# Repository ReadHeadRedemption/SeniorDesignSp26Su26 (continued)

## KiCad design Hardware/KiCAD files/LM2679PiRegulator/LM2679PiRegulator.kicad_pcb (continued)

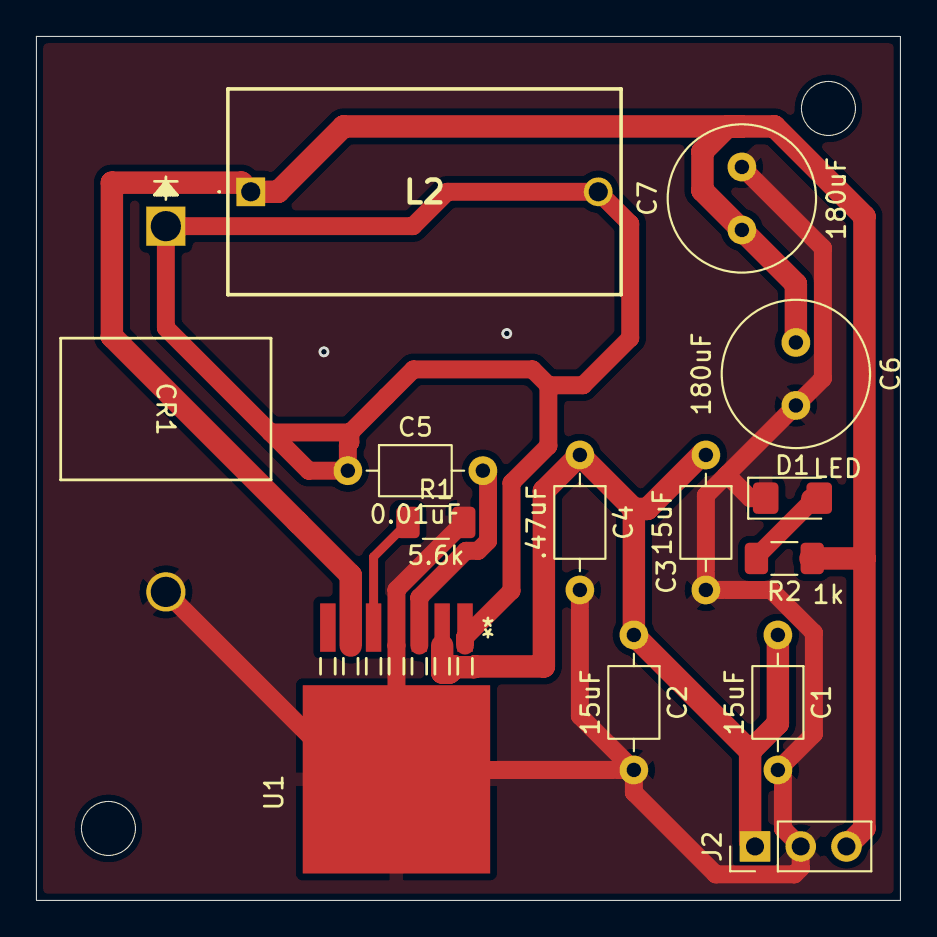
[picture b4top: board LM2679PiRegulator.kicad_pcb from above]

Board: 2 copper layers, 48.0 x 48.0 mm, 14 parts (0 on the bottom side), 7 nets.

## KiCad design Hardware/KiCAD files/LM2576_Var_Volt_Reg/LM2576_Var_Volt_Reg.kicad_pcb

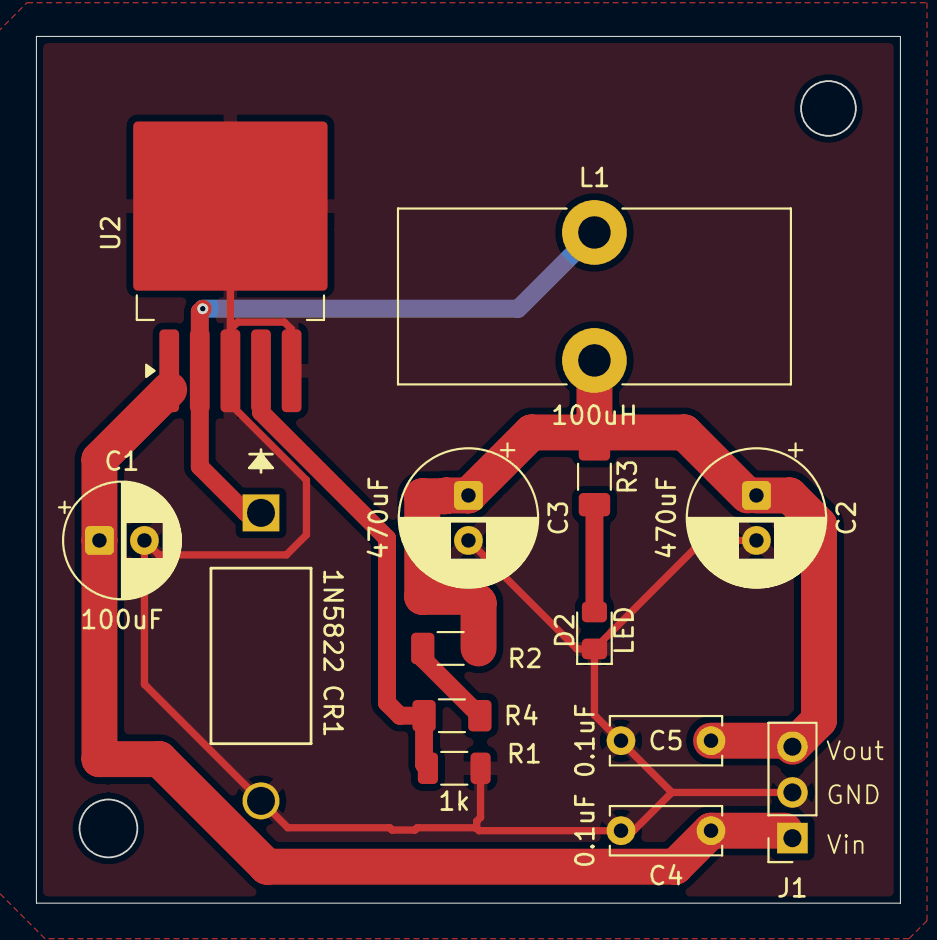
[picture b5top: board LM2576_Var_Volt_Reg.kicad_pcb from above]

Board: 2 copper layers, 48.0 x 48.2 mm, 14 parts (0 on the bottom side), 7 nets.

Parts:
C1: 100uF; CP_Radial_D6.3mm_P2.50mm
C2, C3: 470uF; CP_Radial_D7.5mm_P2.50mm
C4, C5: 0.1uF; C_Disc_D6.0mm_W2.5mm_P5.00mm
CR1: 1N5822; DO-201AD_STM
D2: LED; LED_0805_2012Metric_Pad1.15x1.40mm_HandSolder
J1: Conn_01x03_Pin; PinSocket_1x03_P2.54mm_Vertical
L1: 100uH; L_Toroid_Vertical_L21.6mm_W9.5mm_P7.11mm_Pulse_C
R1: 1k; R_1206_3216Metric
R2: Rvar; R_1206_3216Metric_Pad1.30x1.75mm_HandSolder
R3: 1k; R_1206_3216Metric_Pad1.30x1.75mm_HandSolder
R4: Ropt; R_1206_3216Metric_Pad1.30x1.75mm_HandSolder
U2: LM2576HVS-ADJ; TO-263-5_TabPin3

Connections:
/FB: R1.1, R4.2, U2.4 (FB)
/Vin: C1.1, C4.1, J1.1, U2.1 (VIN)
/Vout: C2.1, C3.1, C5.1, J1.3, L1.2, R2.1, R3.1
GND: C1.2, C2.2, C3.2, C4.2, C5.2, CR1.2, D2.1 (K), J1.2, R1.2, U2.3 (GND), U2.5 (~ON/OFF)
unnamed: D2.2 (A), R3.2
unnamed: R2.2, R4.1
unnamed: CR1.1, L1.1, U2.2 (OUT)

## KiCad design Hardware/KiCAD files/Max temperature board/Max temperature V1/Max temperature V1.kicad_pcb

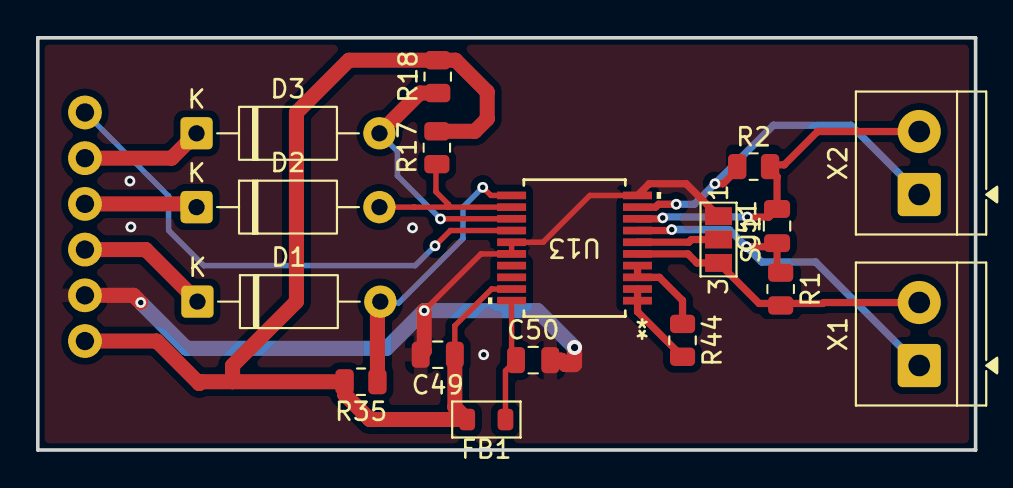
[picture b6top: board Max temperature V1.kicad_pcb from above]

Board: 2 copper layers, 52.1 x 22.9 mm, 18 parts (0 on the bottom side), 17 nets.

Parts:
C49, C50: 0.1uF; C_0805_2012Metric
C51: 100nF; C_0805_2012Metric
D1, D2, D3: 1N4148 eq.; D_A-405_P10.16mm_Horizontal
FB1: FERRITE-0805NO; Ferrite_0805_2012Metric
J1: Conn_01x06; 1x06_P2.54mm
R1, R2: 0ohm; R_0805_2012Metric
R17, R18, R35: 10K; R_0805_2012Metric
R44: 430Ω / 4300Ω 0.1%; R_0805_2012Metric
SJ1: SOLDERJUMPER_2WAY; SolderJumper-3_P1.3mm_Open_Pad1.0x1.5mm_NumberLabels
U13: MAX31865; 21-0056C_20_MXM
X1, X2: 3.5mm; TerminalBlock_4Ucon_1x02_P3.50mm_Horizontal

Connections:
+3.3V: C49.1, FB1.2, J1.6, R17.2, R18.2, R35.2, U13.19 (DVDD)
/CHAINL0_MISO_1: D1.1 (K), J1.4
/MISO_1: J1.1, U13.14 (SDO)
/SPI1_CLK: D2.1 (K), J1.3
/SPI1_CS: D3.1 (K), J1.2
GND: C49.2, C50.2, J1.5, SJ1.1, U13.10 (AGND@2), U13.15 (GND), U13.16 (ANGD@1)
unnamed: D1.2 (A), R35.1, U13.11 (SDI)
unnamed: D2.2 (A), R17.1, U13.12 (SCLK)
unnamed: D3.2 (A), R18.1, U13.13 (CS)
unnamed: C50.1, FB1.1, U13.20 (VDD)
unnamed: R44.2, U13.1 (BIAS), U13.2 (REFIN+)
unnamed: SJ1.2, U13.6 (FORCE2)
unnamed: R1.2, SJ1.3, U13.5 (FORCE+), X1.2
unnamed: R2.1, U13.9 (FORCE-), X2.1
unnamed: R44.1, U13.3 (REFIN-), U13.4 (ISENSOR)
unnamed: C51.1, R1.1, U13.7 (RTDIN+), X1.1
unnamed: C51.2, R2.2, U13.8 (RTDIN-), X2.2

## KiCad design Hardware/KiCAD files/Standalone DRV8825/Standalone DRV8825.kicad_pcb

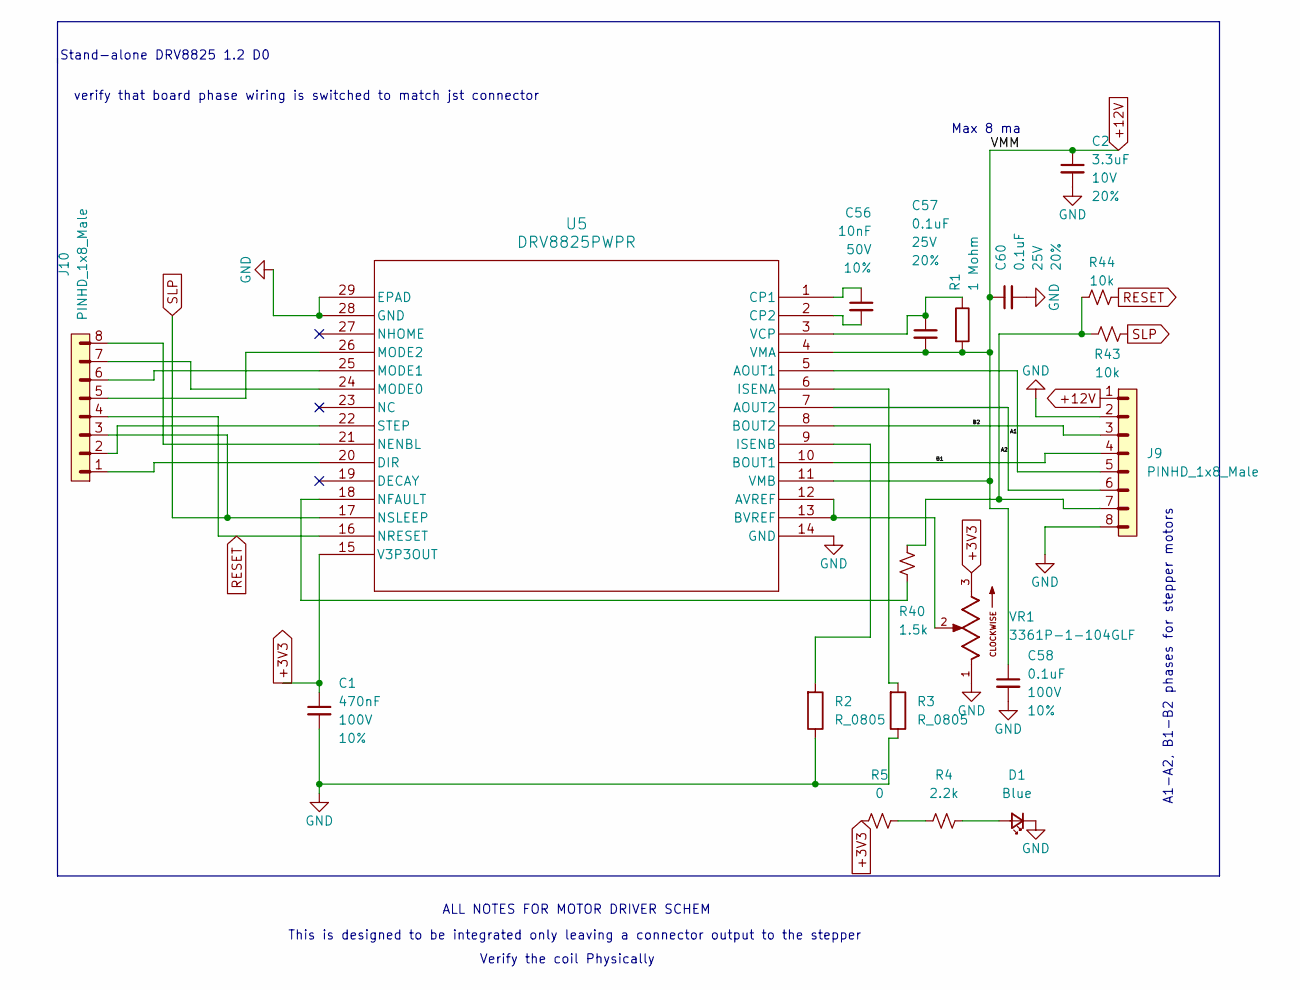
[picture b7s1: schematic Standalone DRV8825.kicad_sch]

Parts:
C1: 470nF; C_0805_2012Metric; Voltage 100V; Tolerance 10%
C2: 3.3uF; C_1206_3216Metric; Voltage 10V; Tolerance 20%
C56: 10nF; C_0603_1608Metric; Voltage 50V; Tolerance 10%
C57, C60: 0.1uF; C_0603_1608Metric; Voltage 25V; Tolerance 20%
C58: 0.1uF; C_0603_1608Metric; Voltage 100V; Tolerance 10%
D1: Blue; LED_0603_1608Metric_Blue
J9, J10: PINHD_1x8_Male; PinHeader_1x08_P2.54mm_Vertical
R1: 1 Mohm; R_0603_1608Metric
R2, R3: R_0805; R_0805_2012Metric
R4: 2.2k; R_0805_2012Metric
R5: 0; R_0805_2012Metric
R40: 1.5k; R_0603_1608Metric
R43, R44: 10k; R_0603_1608Metric
U5: DRV8825PWPR; IC_TPS61196PWPRQ1
VR1: 3361P-1-104GLF; TRIM_3361P-1-104GLF; PARTREV 08/19

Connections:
+3V3: C1.1, R5.1, U5.15 (V3P3OUT), VR1.3
+12V: C2.1, C57.2, C58.1, C60.1, J9.1, R1.1, U5.4 (VMA), U5.11 (VMB)
/A1: J9.5, U5.5 (AOUT1)
/A2: J9.6, U5.7 (AOUT2)
/B1: J9.4, U5.10 (BOUT1)
/B2: J9.3, U5.8 (BOUT2)
GND: C1.2, C2.2, C58.2, C60.2, D1.1 (K), J9.2, J9.8, R2.2, R3.2, U5.14 (GND), U5.28 (GND), U5.29 (EPAD), VR1.1
unnamed: D1.2 (A), R4.2
unnamed: J9.7, R40.2, R43.1, R44.1
unnamed: R4.1, R5.2
unnamed: U5.12 (AVREF), U5.13 (BVREF), VR1.2
unnamed: C56.1, U5.1 (CP1)
unnamed: C56.2, U5.2 (CP2)
unnamed: J10.1, U5.20 (DIR)
unnamed: R3.1, U5.6 (ISENA)
unnamed: R2.1, U5.9 (ISENB)
unnamed: J10.7, U5.24 (MODE0)
unnamed: J10.6, U5.25 (MODE1)
unnamed: J10.5, U5.26 (MODE2)
unnamed: J10.8, U5.21 (NENBL)
unnamed: R40.1, U5.18 (NFAULT)
unnamed: J10.2, U5.22 (STEP)
unnamed: C57.1, R1.2, U5.3 (VCP)
RESET: J10.4, R44.2, U5.16 (NRESET)
SLP: J10.3, R43.2, U5.17 (NSLEEP)

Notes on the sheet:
This is designed to be integrated only leaving a connector output to the stepper
ALL NOTES FOR MOTOR DRIVER SCHEM
verify that board phase wiring is switched to match jst connector
Max 8 ma
A1-A2, B1-B2 phases for stepper motors
Stand-alone DRV8825 1.2 D0
Verify the coil Physically

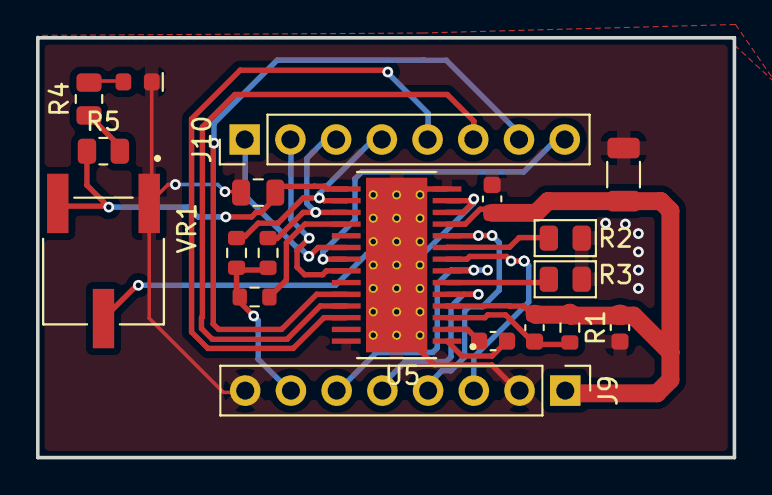
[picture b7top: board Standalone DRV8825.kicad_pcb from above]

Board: 2 copper layers, 38.7 x 23.3 mm, 19 parts (0 on the bottom side), 25 nets.

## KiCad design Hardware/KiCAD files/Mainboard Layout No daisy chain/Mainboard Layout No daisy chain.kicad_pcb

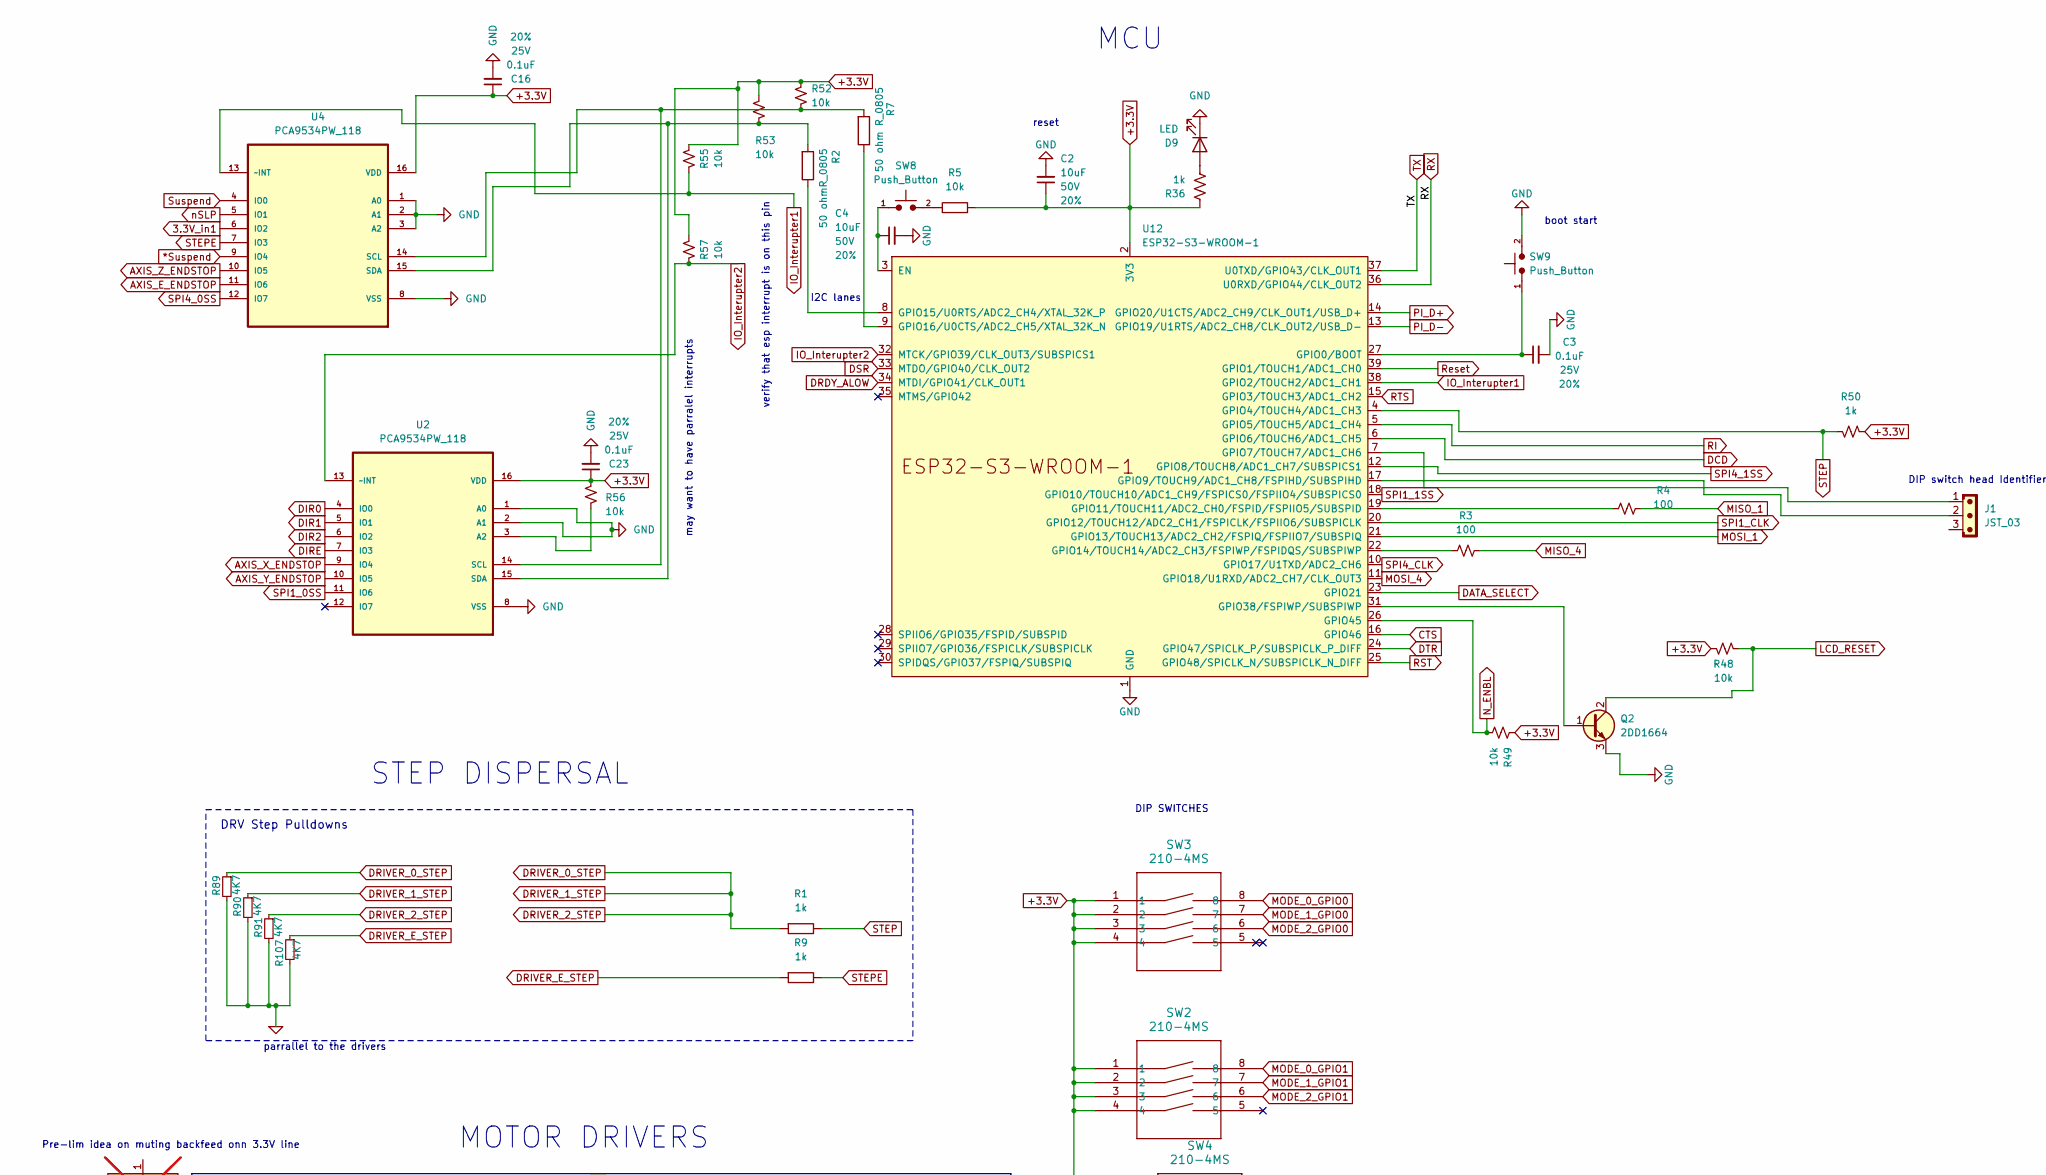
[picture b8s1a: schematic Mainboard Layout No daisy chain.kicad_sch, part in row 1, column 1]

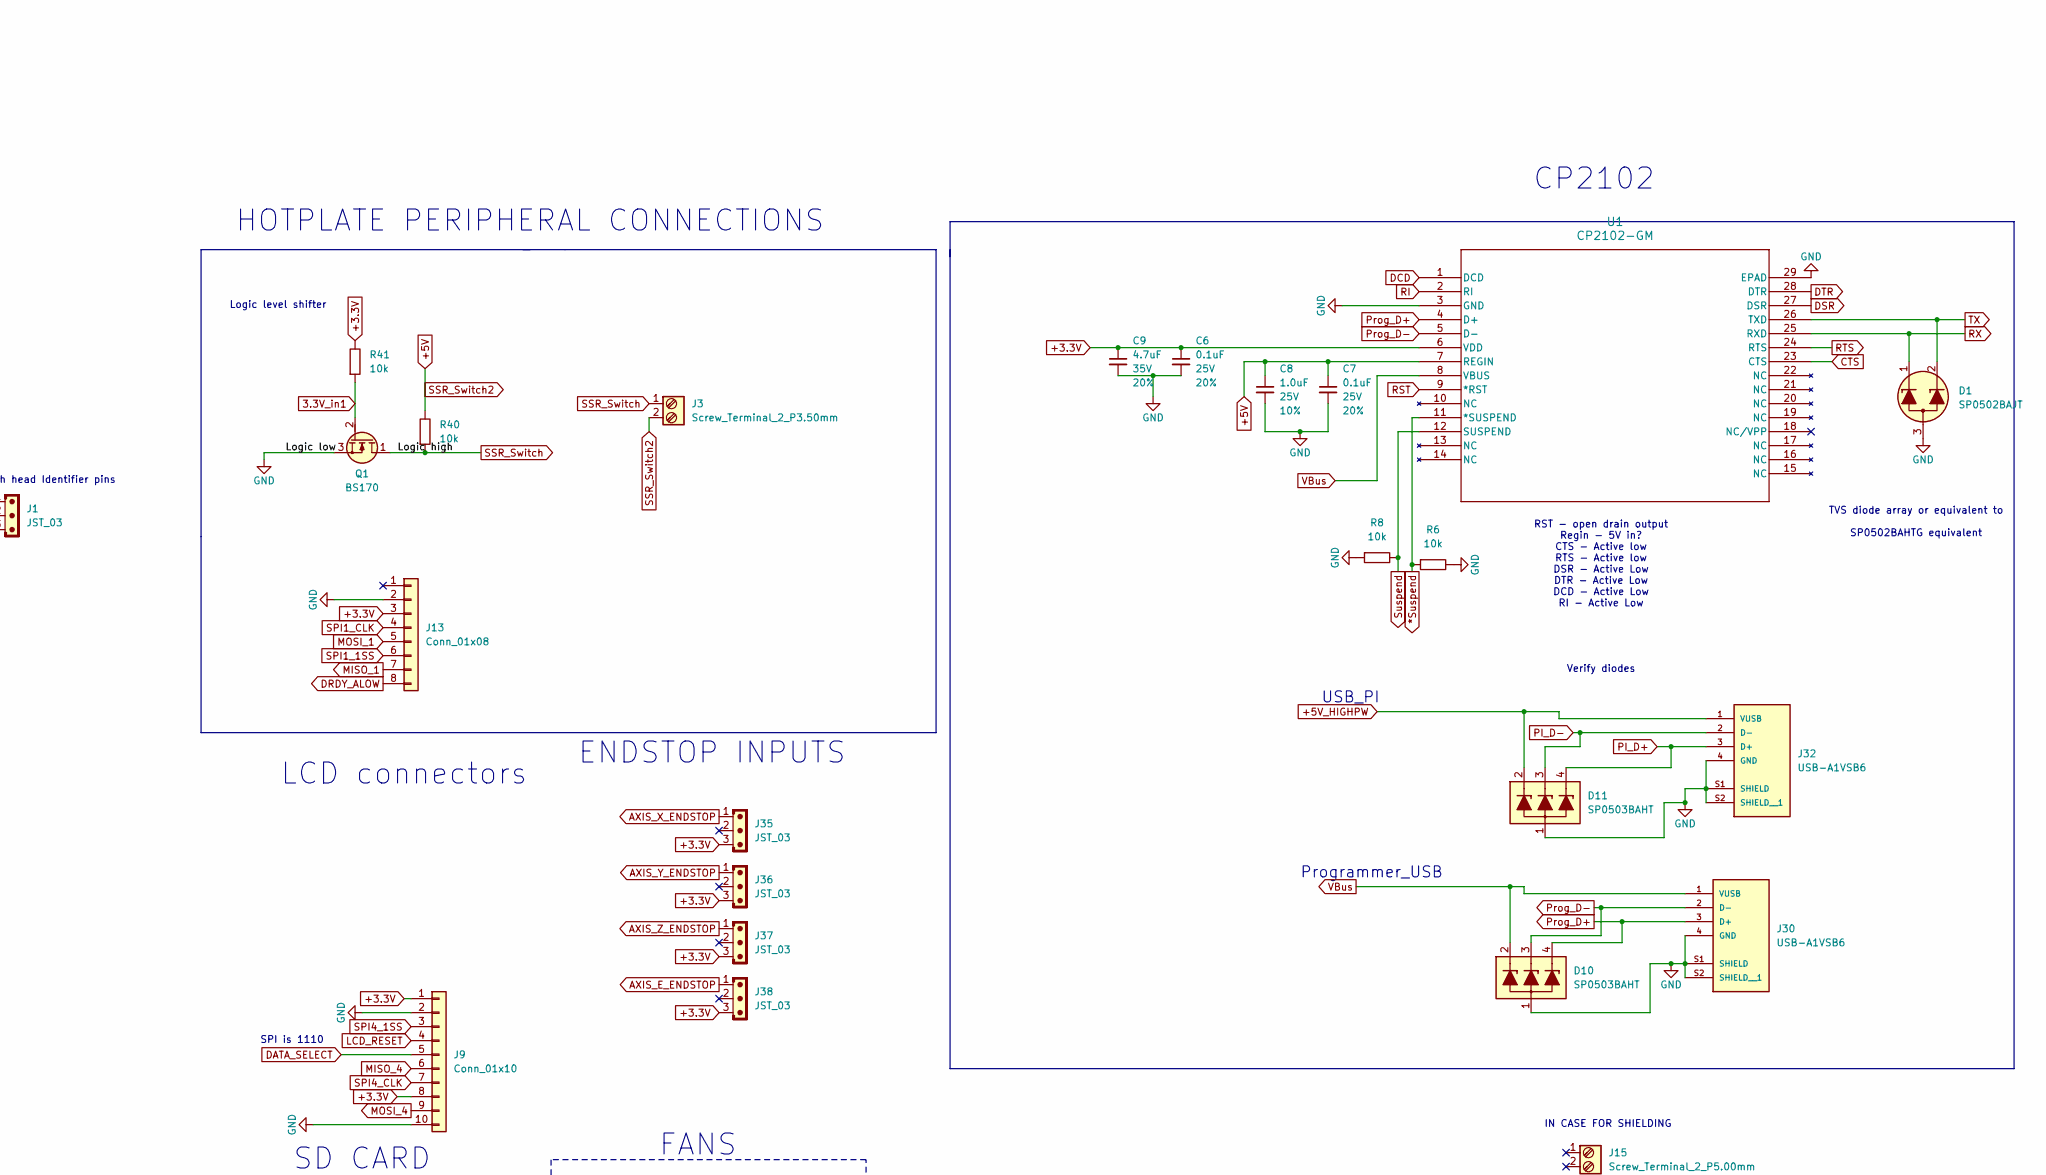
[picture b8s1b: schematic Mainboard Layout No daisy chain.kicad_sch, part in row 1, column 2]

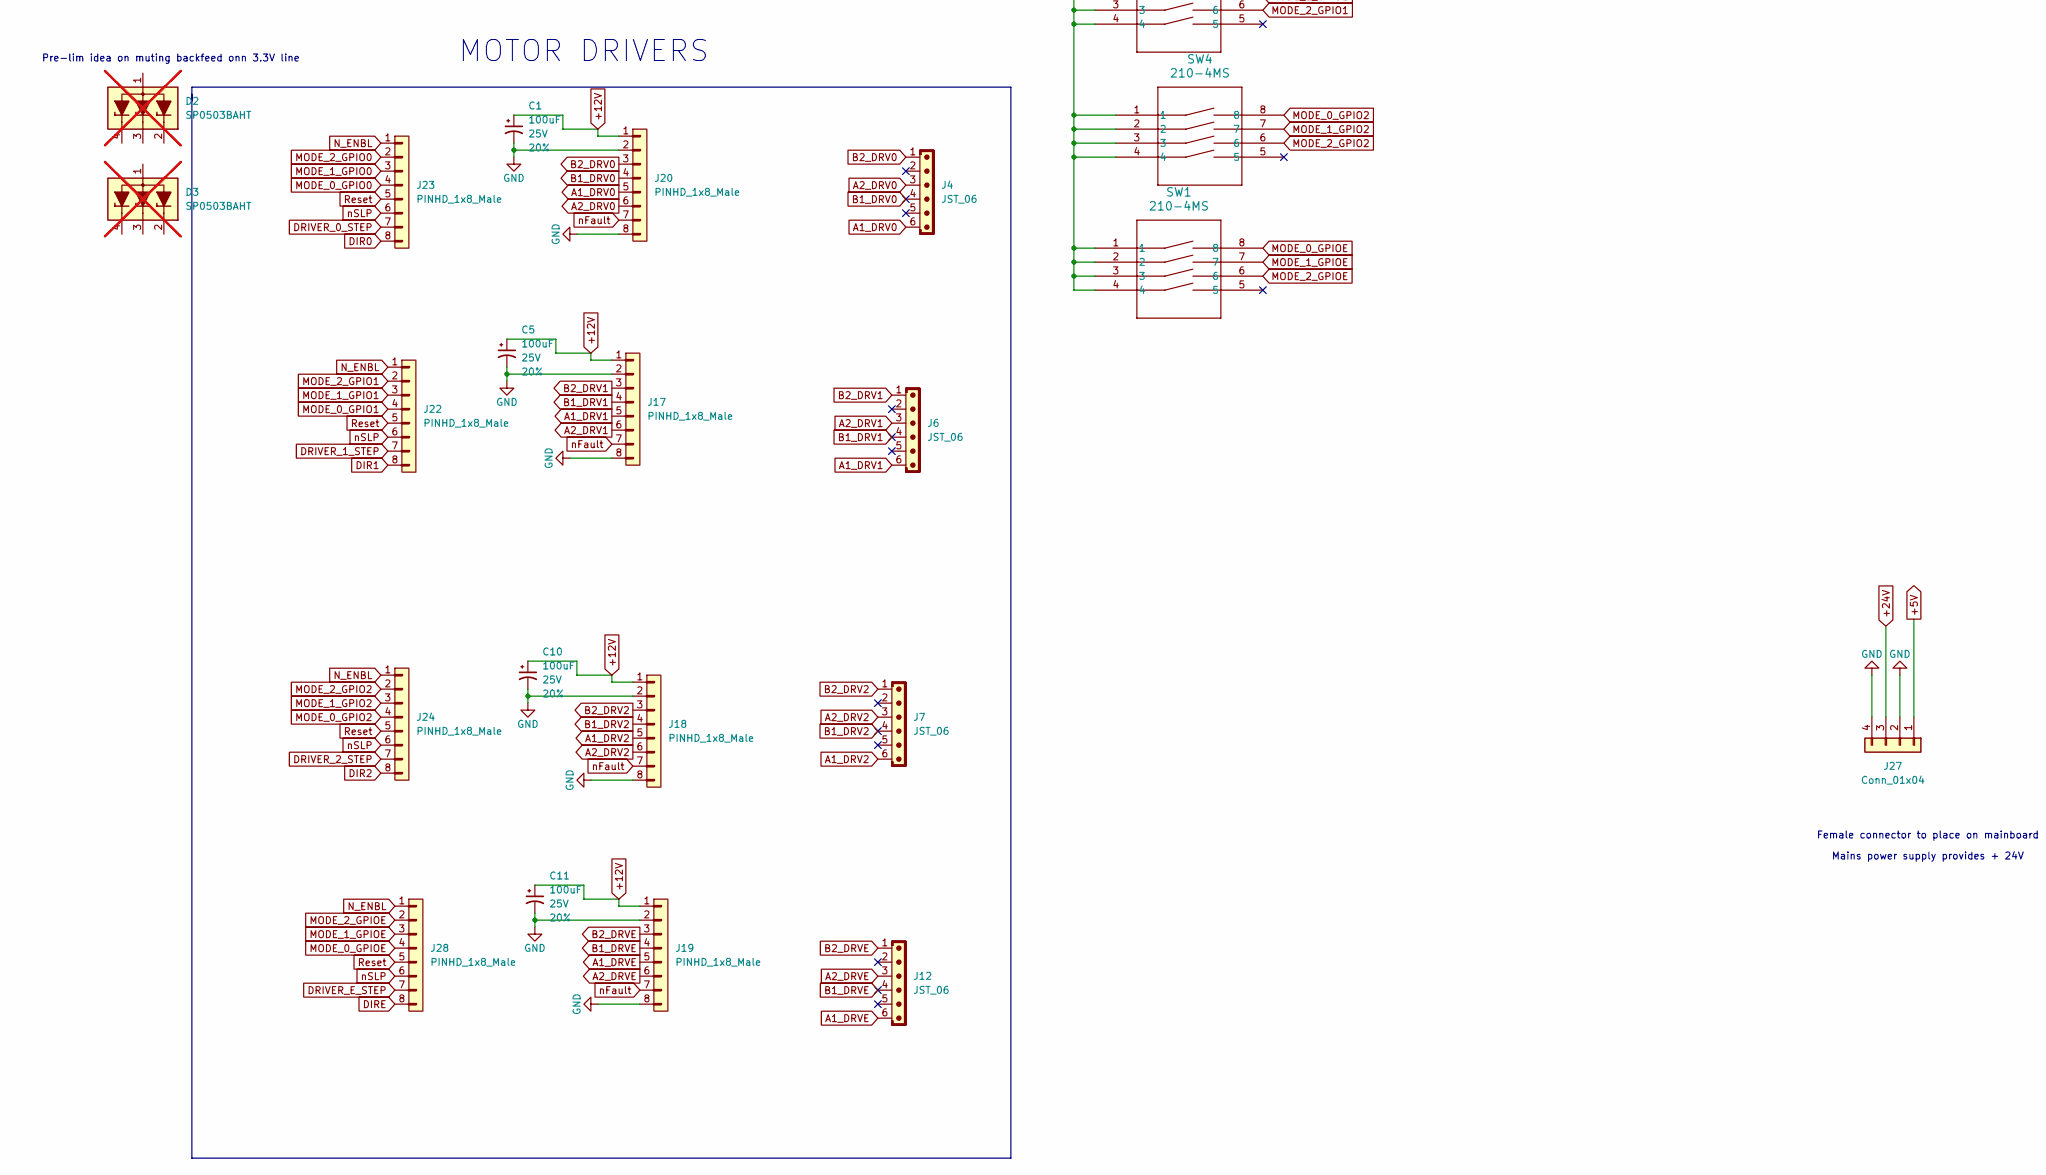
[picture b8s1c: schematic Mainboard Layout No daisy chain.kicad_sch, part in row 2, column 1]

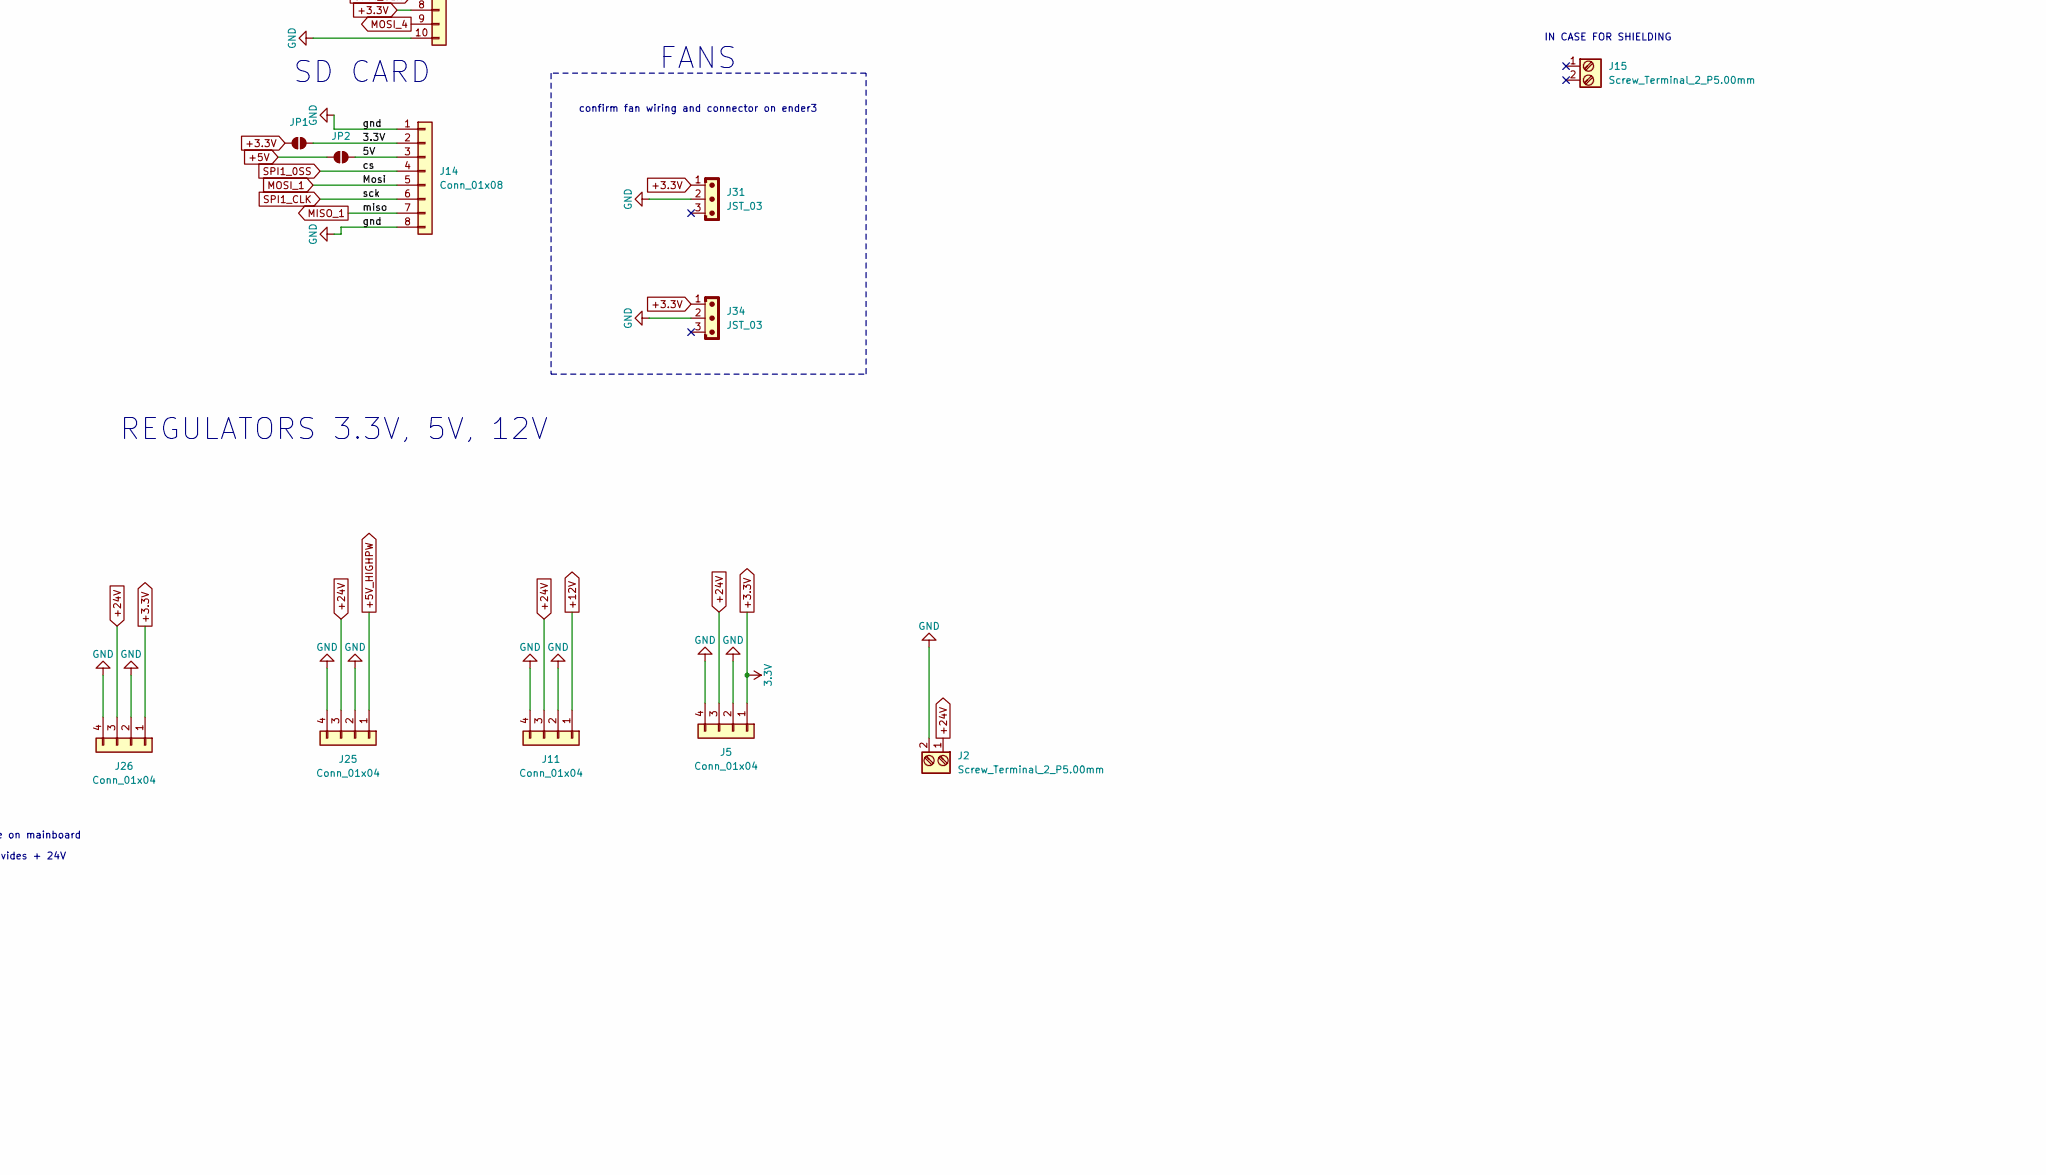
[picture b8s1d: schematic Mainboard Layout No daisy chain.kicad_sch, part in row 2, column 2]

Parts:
C1, C5, C10, C11: 100uF; Panasonic_D; Voltage 25V; Tolerance 20%
C2, C4: 10uF; C_1210_3225Metric; Voltage 50V; Tolerance 20%
C3, C6, C7: 0.1uF; C_0603_1608Metric; Voltage 25V; Tolerance 20%
C8: 1.0uF; C_0805_2012Metric; Voltage 25V; Tolerance 10%
C9: 4.7uF; C_0603_1608Metric; Voltage 35V; Tolerance 20%
C16: 0.1uF; LED_0805_2012Metric; Voltage 25V; Tolerance 20%
C23: 0.1uF; C_0805_2012Metric; Voltage 25V; Tolerance 20%
D1: SP0502BAJT; SOT-323_SC-70
D2, D3: SP0503BAHT; SOT-143; not fitted
D9: LED; LED_0603_1608Metric
D10, D11: SP0503BAHT; SOT-143
J1, J31, J34, J35, J36, J37, J38: JST_03; JST_EH_B3B-EH-A_1x03_P2.50mm_Vertical
J2, J15: Screw_Terminal_2_P5.00mm; TerminalBlock_Phoenix_PT-1,5-2-5.0-H_1x02_P5.00mm_Horizontal
J3: Screw_Terminal_2_P3.50mm; TerminalBlock_Phoenix_PT-1,5-2-3.5-H_1x02_P3.50mm_Horizontal
J4, J6, J7, J12: JST_06; JST_EH_B6B-EH-A_1x06_P2.50mm_Vertical
J5, J11, J25, J26, J27: Conn_01x04; 1x04_P2.54mm
J9: Conn_01x10; 1x10_P2.54mm
J13, J14: Conn_01x08; 1x08_P2.54mm
J17, J18, J19, J20, J22, J23, J24, J28: PINHD_1x8_Male; PinHeader_1x08_P2.54mm_Vertical
J30, J32: USB-A1VSB6; USB_A_Kycon_KUSBX-AS1N-B_Horizontal; PARTREV D
JP1, JP2: Jumper_2_NO
Q1: BS170; TO-92_Inline_Wide_DGS
Q2: 2DD1664; SOT-89-3
R1, R50: 1k; R_Axial_DIN0207_L6.3mm_D2.5mm_P10.16mm_Horizontal
R2: 50 ohmR_0805; R_0805_2012Metric
R3, R4: 100; R_0603_1608Metric
R5, R6, R8, R40, R41: 10k; R_Axial_DIN0207_L6.3mm_D2.5mm_P10.16mm_Horizontal
R7: 50 ohm R_0805; R_0805_2012Metric
R9: 1k; R_0805_2012Metric
R36: 1k; R_1206_3216Metric_Pad1.30x1.75mm_HandSolder
R48, R49: 10k; R_0603_1608Metric
R52, R53: 10k; LED_0805_2012Metric
R55, R56, R57: 10k; R_0805_2012Metric
R89, R90, R91, R107: 4K7; R_0603_1608Metric; Part Number RK73H1ETTP4701F
SW1, SW2, SW3, SW4: 210-4MS; DIP8_210-4_CTS
SW8, SW9: Push_Button; SW_PUSH_6mm
U1: CP2102-GM; QFN28_5X5_SIL
U2, U4: PCA9534PW_118; SOP65P640X110-16N; MPN PCA9534PW,118
U12: ESP32-S3-WROOM-1

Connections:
3.3V_in1: Q1.2 (G), R41.1, U4.6 (IO2)
*Suspend: R6.1, U1.11 (*SUSPEND), U4.9 (IO4)
+3.3V: C2.1, C6.1, C9.1, C16.1, C23.1, J5.1, J9.1, J9.8, J13.3, J14.2, J26.1, J31.1, J34.1, J35.3, J36.3, J37.3, J38.3, JP1.1 (A), JP1.2 (B), R5.1, R36.1, R41.2, R48.1, R49.2, R50.2, R52.2, R53.2, R55.1, R56.2, R57.1, SW1.1, SW1.2, SW1.3, SW1.4, SW2.1, SW2.2, SW2.3, SW2.4, SW3.1, SW3.2, SW3.3, SW3.4, SW4.1, SW4.2, SW4.3, SW4.4, U1.6 (VDD), U2.16 (VDD), U4.16 (VDD), U12.2 (3V3)
+5V: C7.1, C8.1, J3.2, J27.1, JP2.1 (A), R40.2, U1.7 (REGIN)
+5V_HIGHPW: D11.2 (L1), J25.1, J32.1 (VUSB)
+12V: C1.1, C5.1, C10.1, C11.1, J11.1, J17.1, J18.1, J19.1, J20.1
+24V: J2.1, J5.3, J11.3, J25.3, J26.3, J27.3
/5V: J14.3, JP2.2 (B)
A1_DRV0: J4.6, J20.5
A1_DRV1: J6.6, J17.5
A1_DRV2: J7.6, J18.5
A1_DRVE: J12.6, J19.5
A2_DRV0: J4.3, J20.6
A2_DRV1: J6.3, J17.6
A2_DRV2: J7.3, J18.6
A2_DRVE: J12.3, J19.6
AXIS_E_ENDSTOP: J38.1, U4.11 (IO6)
AXIS_X_ENDSTOP: J35.1, U2.9 (IO4)
AXIS_Y_ENDSTOP: J36.1, U2.10 (IO5)
AXIS_Z_ENDSTOP: J37.1, U4.10 (IO5)
B1_DRV0: J4.4, J20.4
B1_DRV1: J6.4, J17.4
B1_DRV2: J7.4, J18.4
B1_DRVE: J12.4, J19.4
B2_DRV0: J4.1, J20.3
B2_DRV1: J6.1, J17.3
B2_DRV2: J7.1, J18.3
B2_DRVE: J12.1, J19.3
CTS: U1.23 (CTS), U12.16 (GPIO46)
DATA_SELECT: J9.5, U12.23 (GPIO21)
DCD: U1.1 (DCD), U12.6 (GPIO6/TOUCH6/ADC1_CH5)
DIR0: J23.8, U2.4 (IO0)
DIR1: J22.8, U2.5 (IO1)
DIR2: J24.8, U2.6 (IO2)
DIRE: J28.8, U2.7 (IO3)
DRDY_ALOW: J13.8, U12.34 (MTDI/GPIO41/CLK_OUT1)
DRIVER_0_STEP: J22.7, J23.7, J24.7, R1.1, R89.1, R90.1, R91.1
DRIVER_E_STEP: J28.7, R9.1, R107.1
DSR: U1.27 (DSR), U12.33 (MTDO/GPIO40/CLK_OUT2)
DTR: U1.28 (DTR), U12.24 (GPIO47/SPICLK_P/SUBSPICLK_P_DIFF)
GND: C1.2, C2.2, C3.2, C4.2, C5.2, C6.2, C7.2, C8.2, C9.2, C10.2, C11.2, C16.2, C23.2, D1.3 (A), D9.1 (K), D10.1 (VN), D11.1 (VN), J2.2, J5.2, J5.4, J9.2, J9.10, J11.2, J11.4, J13.2, J14.1, J14.8, J17.2, J17.8, J18.2, J18.8, J19.2, J19.8, J20.2, J20.8, J25.2, J25.4, J26.2, J26.4, J27.2, J27.4, J30.4 (GND), J30.S1 (SHIELD), J30.S2 (SHIELD__1), J31.2, J32.4 (GND), J32.S1 (SHIELD), J32.S2 (SHIELD__1), J34.2, Q1.3 (S), Q2.3 (E), R6.2, R8.1, R89.2, R90.2, R91.2, R107.2, SW9.2, U1.3 (GND), U1.29 (EPAD), U2.1 (A0), U2.2 (A1), U2.8 (VSS), U4.1 (A0), U4.2 (A1), U4.3 (A2), U4.8 (VSS), U12.1 (GND), U12.40 (GND), U12.41 (GND)
IO_Interupter1: R55.2, U4.13 (~INT), U12.38 (GPIO2/TOUCH2/ADC1_CH1)
IO_Interupter2: R57.2, U2.13 (~INT), U12.32 (MTCK/GPIO39/CLK_OUT3/SUBSPICS1)
LCD_RESET: J9.4, Q2.2 (C), R48.2
MISO_1: J13.7, J14.7, R4.2
MISO_4: J9.6, R3.2
MODE_0_GPIO0: J23.4, SW3.8
MODE_0_GPIO1: J22.4, SW2.8
MODE_0_GPIO2: J24.4, SW4.8
MODE_0_GPIOE: J28.4, SW1.8
MODE_1_GPIO0: J23.3, SW3.7
MODE_1_GPIO1: J22.3, SW2.7
MODE_1_GPIO2: J24.3, SW4.7
MODE_1_GPIOE: J28.3, SW1.7
MODE_2_GPIO0: J23.2, SW3.6
MODE_2_GPIO1: J22.2, SW2.6
MODE_2_GPIO2: J24.2, SW4.6
MODE_2_GPIOE: J28.2, SW1.6
MOSI_1: J13.5, J14.5, U12.21 (GPIO13/TOUCH13/ADC2_CH2/FSPIQ/FSPIIO7/S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)
MOSI_4: J9.9, U12.11 (GPIO18/U1RXD/ADC2_CH7/CLK_OUT3)
N_ENBL: J22.1, J23.1, J24.1, J28.1, R49.1, U12.26 (GPIO45)
unnamed: D9.2 (A), R36.2
unnamed: Q2.1 (B), U12.31 (GPIO38/FSPIWP/SUBSPIWP)
unnamed: R5.2, SW8.2
unnamed: R56.1, U2.3 (A2)
unnamed: R7.1, R52.1, U2.14 (SCL), U4.14 (SCL)
unnamed: R2.1, R53.1, U2.15 (SDA), U4.15 (SDA)
unnamed: C4.1, SW8.1, U12.3 (EN)
unnamed: C3.1, SW9.1, U12.27 (GPIO0/BOOT)
unnamed: J1.1, U12.7 (GPIO7/TOUCH7/ADC1_CH6)
unnamed: J1.2, U12.17 (GPIO9/TOUCH9/ADC1_CH8/FSPIHD/SUBSPIHD)
unnamed: R4.1, U12.19 (GPIO11/TOUCH11/ADC2_CH0/FSPID/FSPIIO5/S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)
unnamed: R3.1, U12.22 (GPIO14/TOUCH14/ADC2_CH3/FSPIWP/FSPIDQS/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)
unnamed: R2.2, U12.8 (GPIO15/U0RTS/ADC2_CH4/XTAL_32K_P)
unnamed: R7.2, U12.9 (GPIO16/U0CTS/ADC2_CH5/XTAL_32K_N)
PI_D+: D11.4 (L3), J32.3 (D+), U12.14 (GPIO20/U1CTS/ADC2_CH9/CLK_OUT1/USB_D+)
PI_D-: D11.3 (L2), J32.2 (D-), U12.13 (GPIO19/U1RTS/ADC2_CH8/CLK_OUT2/USB_D-)
Prog_D+: D10.4 (L3), J30.3 (D+), U1.4 (D+)
Prog_D-: D10.3 (L2), J30.2 (D-), U1.5 (D-)
RI: U1.2 (RI), U12.5 (GPIO5/TOUCH5/ADC1_CH4)
RST: U1.9 (*RST), U12.25 (GPIO48/SPICLK_N/SUBSPICLK_N_DIFF)
RTS: U1.24 (RTS), U12.15 (GPIO3/TOUCH3/ADC1_CH2)
RX: D1.1 (K1), U1.25 (RXD), U12.36 (U0RXD/GPIO44/CLK_OUT2)
Reset: J22.5, J23.5, J24.5, J28.5, U12.39 (GPIO1/TOUCH1/ADC1_CH0)
SPI1_0SS: J14.4, U2.11 (IO6)
SPI1_1SS: J13.6, U12.18 (GPIO10/TOUCH10/ADC1_CH9/FSPICS0/FSPIIO4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)
SPI1_CLK: J13.4, J14.6, U12.20 (GPIO12/TOUCH12/ADC2_CH1/FSPICLK/FSPIIO6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)
SPI4_0SS: U4.12 (IO7)
SPI4_1SS: J9.3, U12.12 (GPIO8/TOUCH8/ADC1_CH7/SUBSPICS1)
SPI4_CLK: J9.7, U12.10 (GPIO17/U1TXD/ADC2_CH6)
SSR_Switch: J3.1, Q1.1 (D), R40.1
STEP: R1.2, R50.1, U12.4 (GPIO4/TOUCH4/ADC1_CH3)
STEPE: R9.2, U4.7 (IO3)
Suspend: R8.2, U1.12 (SUSPEND), U4.4 (IO0)
TX: D1.2 (K2), U1.26 (TXD), U12.37 (U0TXD/GPIO43/CLK_OUT1)
VBus: D10.2 (L1), J30.1 (VUSB), U1.8 (VBUS)
nFault: J17.7, J18.7, J19.7, J20.7
nSLP: J22.6, J23.6, J24.6, J28.6, U4.5 (IO1)

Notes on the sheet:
verify that esp interrupt is on this pin
USB_PI
Pre-lim idea on muting backfeed onn 3.3V line
MCU
REGULATORS 3.3V, 5V, 12V
IN CASE FOR SHIELDING
Female connector to place on mainboard
RST - open drain output Regin - 5V in? CTS - Active low RTS - Active low DSR - Active Low DTR - Active Low DCD - Active Low RI - Active Low
Mains power supply provides + 24V
DIP SWITCHES
SD CARD
HOTPLATE PERIPHERAL CONNECTIONS
SPI is 1110
boot start
confirm fan wiring and connector on ender3
Programmer_USB
FANS
TVS diode array or equivalent to SP0502BAHTG equivalent
Logic level shifter
Verify diodes
reset
may want to have parralel interrupts
LCD connectors
I2C lanes
DIP switch head Identifier pins
CP2102
parrallel to the drivers
MOTOR DRIVERS
DRV Step Pulldowns
STEP DISPERSAL
ENDSTOP INPUTS

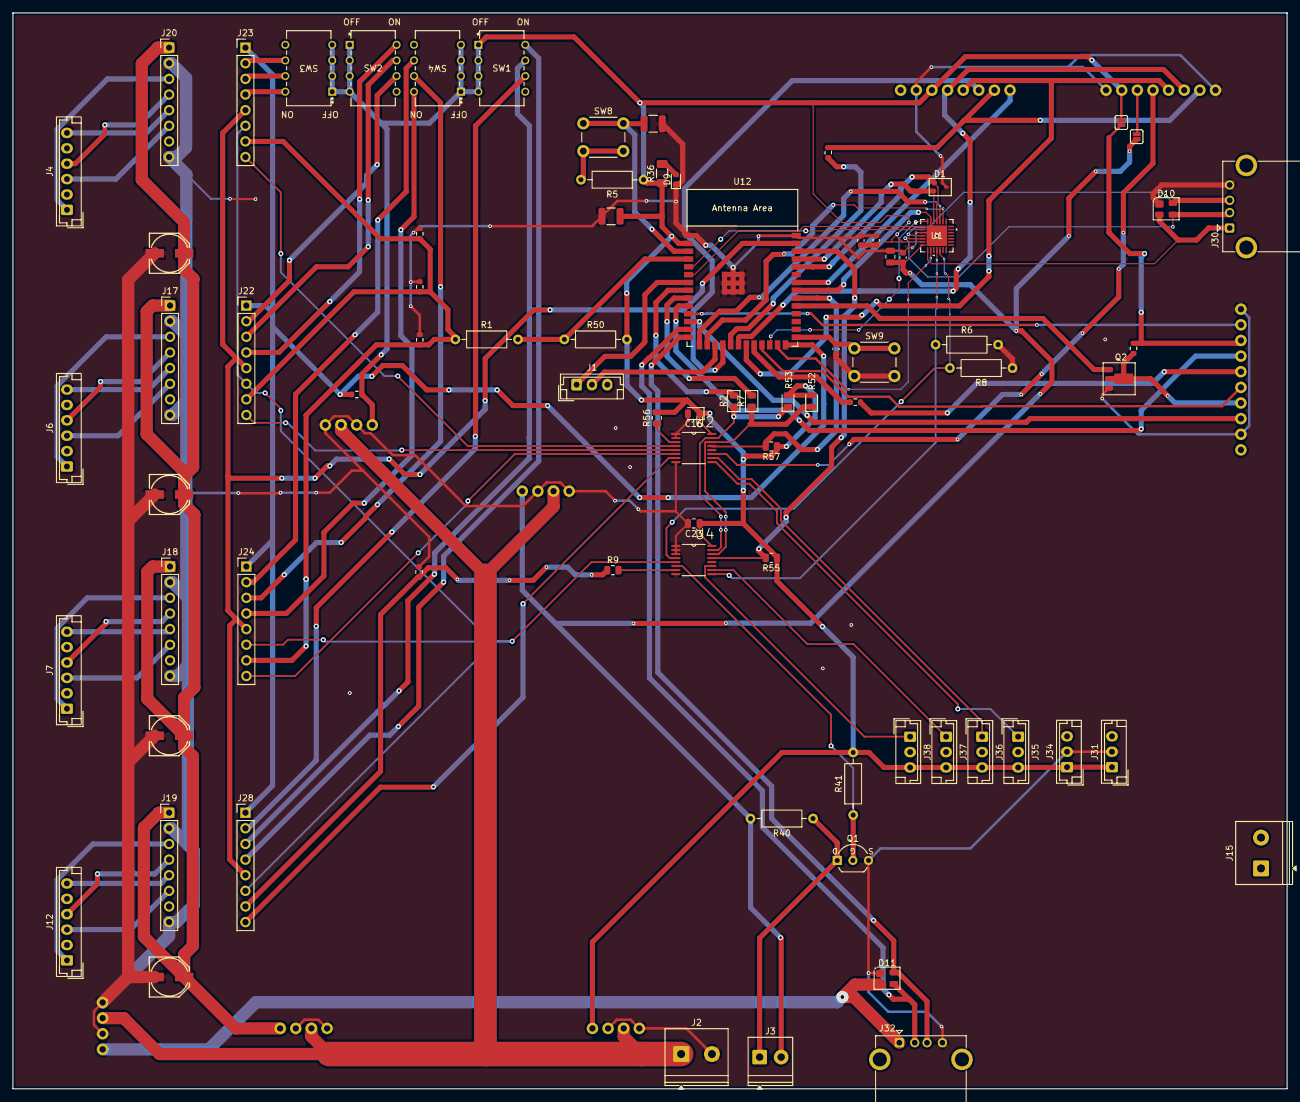
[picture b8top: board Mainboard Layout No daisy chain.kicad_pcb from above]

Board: 2 copper layers, 207.0 x 174.8 mm, 87 parts (0 on the bottom side), 97 nets.
